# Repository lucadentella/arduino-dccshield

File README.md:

# DCCShield for Arduino

Optocoupled interface to connect Arduino to the DCC bus.

Available both as an Arduino shield and as a standalone board.

*Interfaccia optoisolata per collegare Arduino al bus DCC.*

*Disponibile sia come shield Arduino che come scheda autonoma.*

## Firmware

In the Arduino folder, a basic sketch is available to implement a DCC decoder as explained in the video.

*Nella cartella Arduino, è disponibile un semplice sketch per implementare un decoder DCC come illustrato nel video.*

## Documentation

 - [Tutorial in **English**](https://youtu.be/aA6cgGWZWBE) (Youtube)
 - [Tutorial in **Italiano**](https://youtu.be/_3cTWvrFvNA) (Youtube)

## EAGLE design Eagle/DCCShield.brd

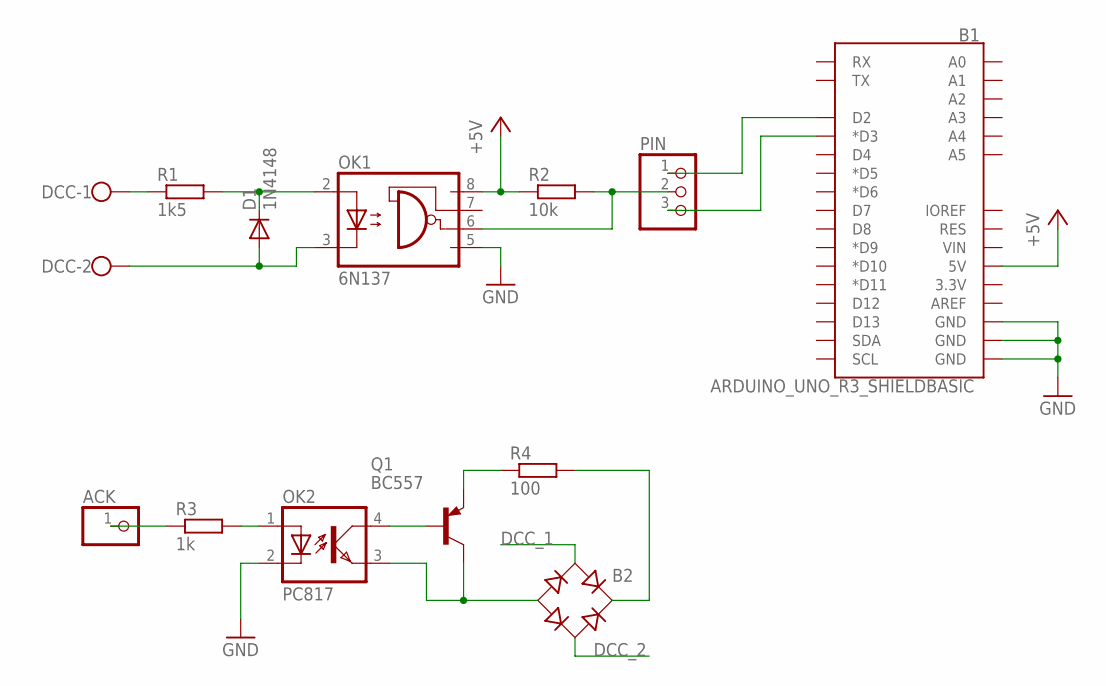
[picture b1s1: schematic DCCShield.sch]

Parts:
ACK: PINHD-1X1; 1X01
B1: ARDUINO_UNO_R3_SHIELDBASIC; UNO_R3_SHIELD
B2: RB1A
D1: 1N4148; DO35-10
DCC: W237-102
OK1: 6N137; DIL08
OK2: PC817; DIL04
PIN: PINHD-1X3; 1X03
Q1: BC557; TO92
R1: 1k5; 0207/10
R2: 10k; 0207/10
R3: 1k; 0207/10
R4: 100; 0207/10

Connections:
+5V: B1.5V, OK1.8 (VCC), R2.1
DCC_1: B2.AC1, DCC.1, R1.1
DCC_2: B2.AC2, D1.A, DCC.2, OK1.3 (C)
GND: B1.GND@0 (GND), B1.GND@1 (GND), B1.GND@2 (GND), OK1.5 (GND), OK2.2 (C)
unnamed: B2.-, OK2.3 (EMIT), Q1.3 (C)
unnamed: D1.C, OK1.2 (A), R1.2
unnamed: ACK.1, R3.1
unnamed: OK1.6 (VO), PIN.2, R2.2
unnamed: B1.D2, PIN.1
unnamed: B1.D3 (*D3), PIN.3
unnamed: OK2.1 (A), R3.2
unnamed: OK2.4 (COL), Q1.2 (B)
unnamed: Q1.1 (E), R4.1
unnamed: B2.+, R4.2

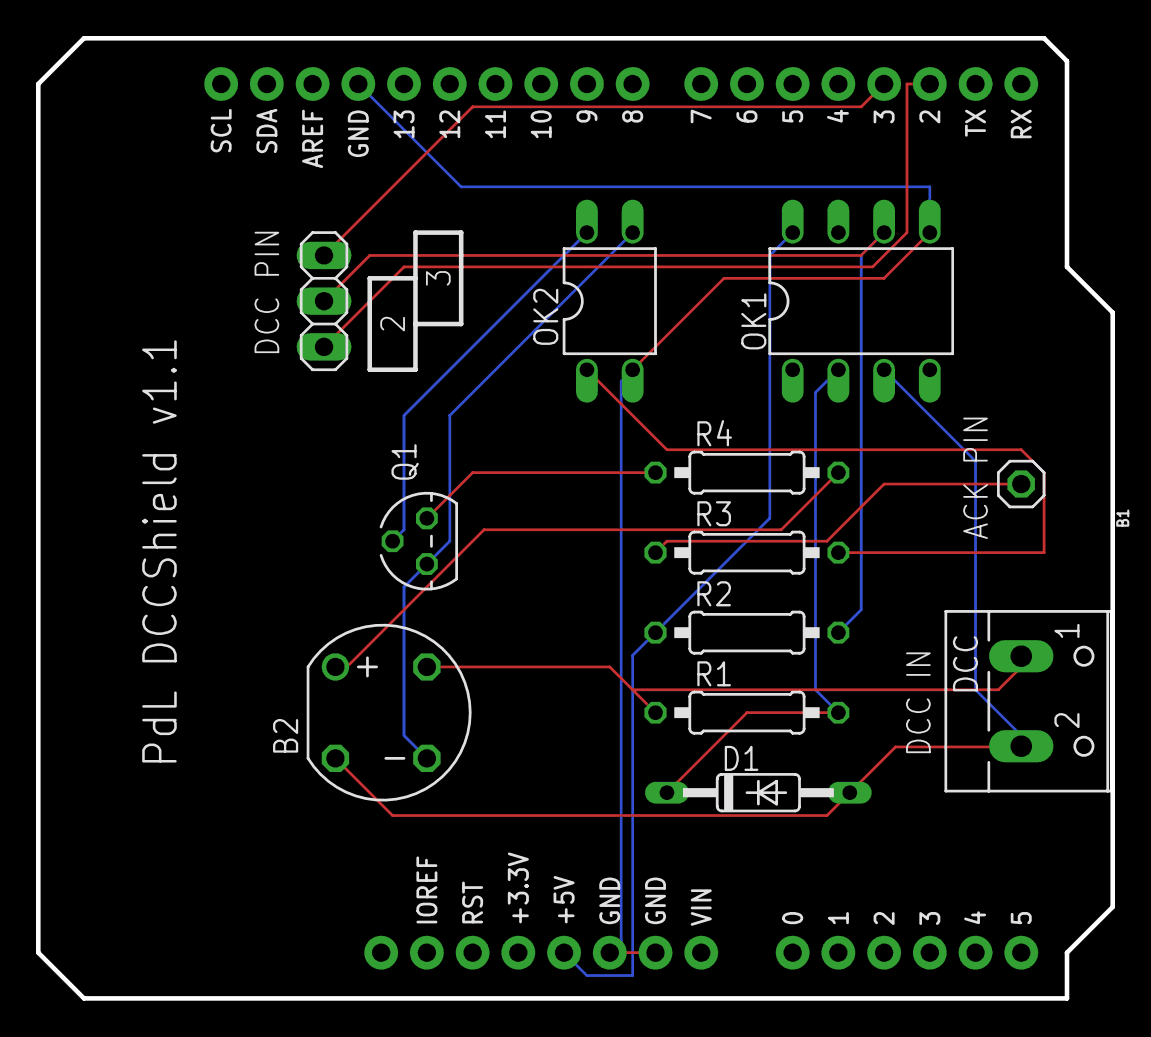
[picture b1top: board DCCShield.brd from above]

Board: 2 copper layers, 59.7 x 53.3 mm, 13 parts (0 on the bottom side), 14 nets.

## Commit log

2020-11-23 Standalone interface added
2020-11-23 Readme and sketch updated
2020-11-23 Updated README with youtube links
2021-05-13 Create Arduino build workflow
2021-05-13 Sketch moved into dedicated folder
2021-05-13 Workflow triggered by push events
2022-09-02 Variable address (and corresponding CV) added
2025-03-01 Updated to ver 1.1

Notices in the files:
parts and their libraries:
SparkFun-Boards: Licensing: Creative Commons ShareAlike 4.0 International - https://creativecommons.org/licenses/by-sa/4.0
